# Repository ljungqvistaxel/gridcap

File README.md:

# Robust Positional Force Sensing Using Metal Over Capacitive Touch

This repository contains software, PCB design files, and 3D models used in the research with the title as above, as well as the collected data. The research investigates the use of metal over cap in a 2D matrix to meassure applied force at different parts of the sensor module. The data collected ad used in the research is also included in this repository.

## Used hardware and components

Gridcap module: 
- stm32f401re, charges/discharges pads and reads charging time with a 11.9 ns resolution, and sends the pads charging time over UART.
- 20x20 aluminium extrution (any standard length works, as long as its long enough).
- 220 kOhm resistor for pad charging.
- 74HC4067PW-Q100J MUX (4x), found at: https://www.mouser.se/ProductDetail/Nexperia/74HC4067PW-Q100J?qs=sPdA%252BpIfi%2F%252BXvXN1KGf9sg%3D%3D
- 0.5mm, 0.7mm or 1.0mm thich aluminium metal sheet (110mm x 110mm).
- SN74HC14N schmitt trigger, found at: https://www.digikey.se/sv/products/detail/texas-instruments/SN74HC14N/277223

Test rig:
- HX711 loadcell amplifier, found at: https://www.electrokit.com/forstarkare-for-lastceller-hx711
- 10kg rated loadcell, found at: https://www.electrokit.com/lastcell-10kg

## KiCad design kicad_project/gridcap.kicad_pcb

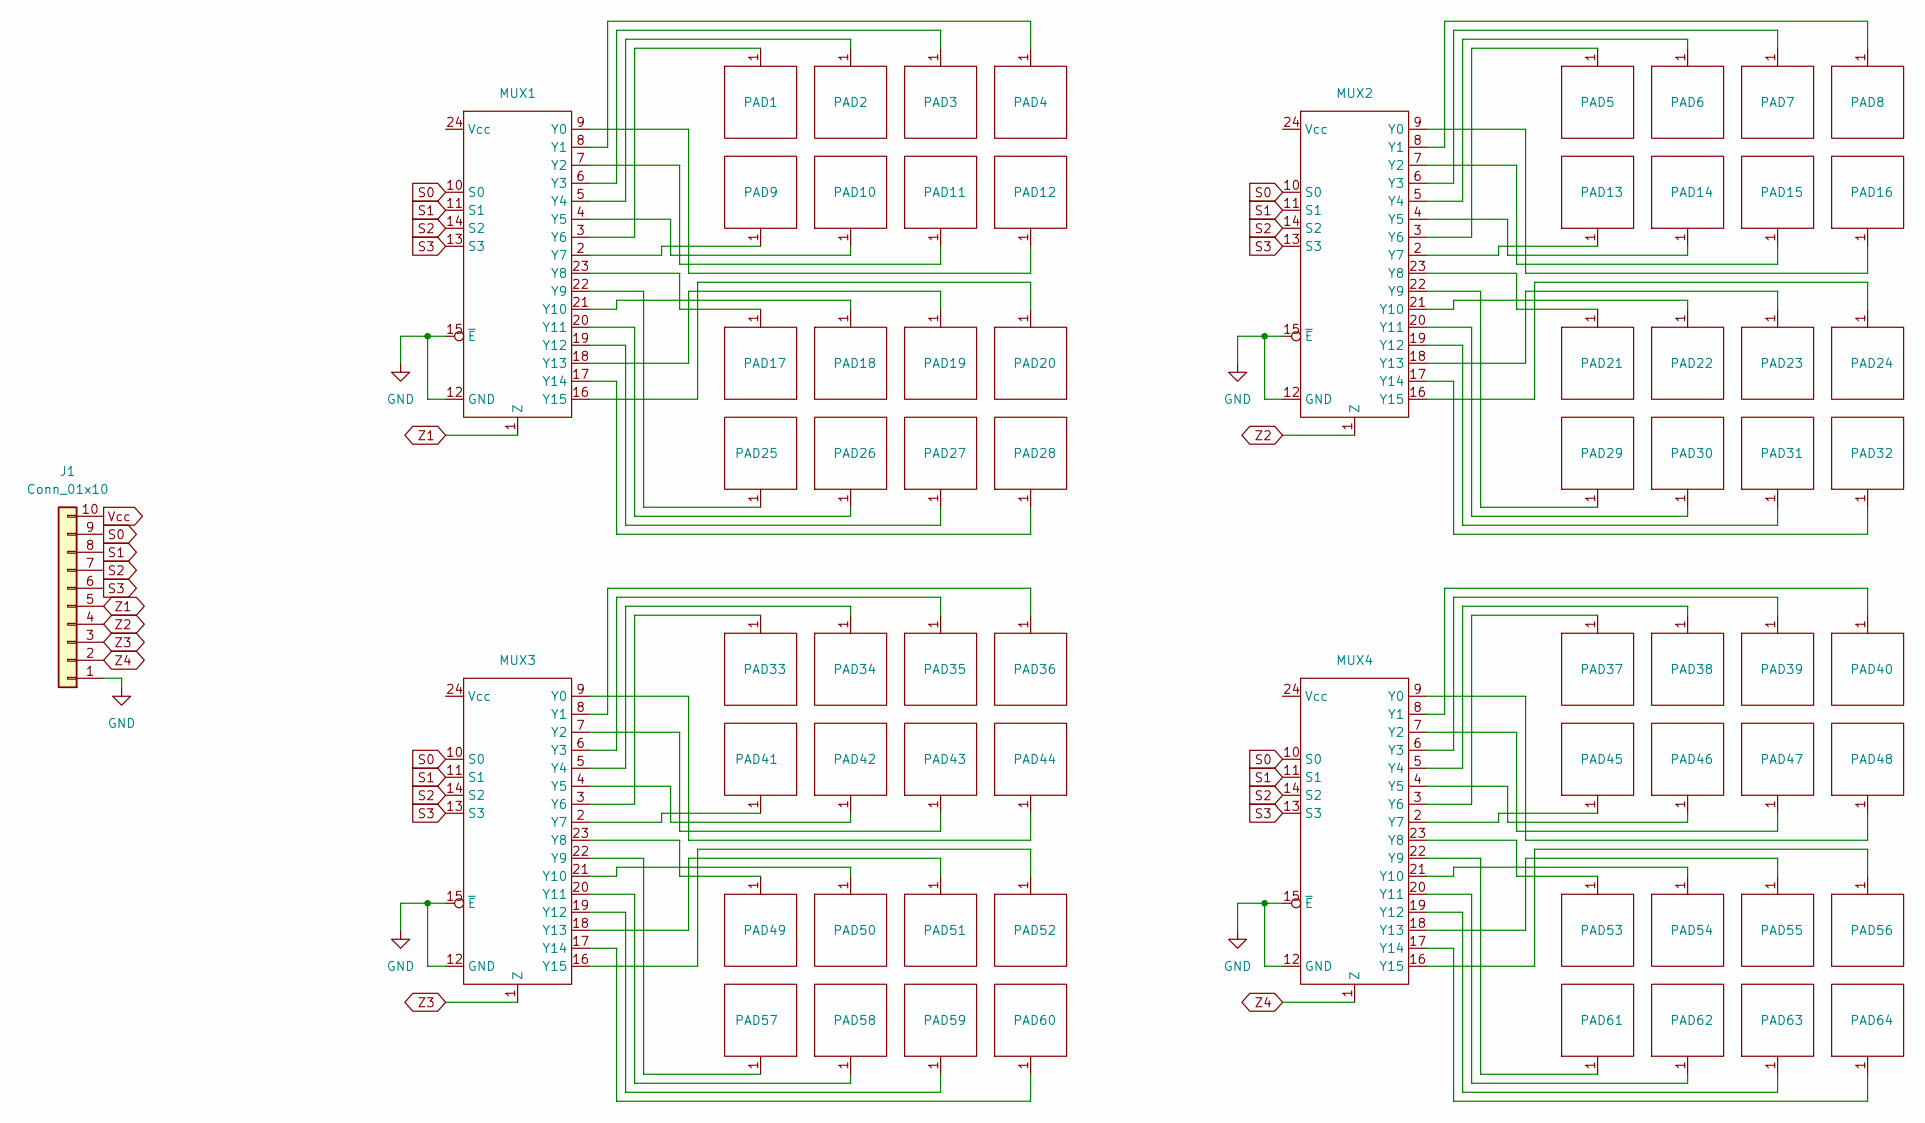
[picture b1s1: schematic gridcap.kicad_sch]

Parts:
J1: Conn_01x10
MUX1, MUX2, MUX3, MUX4: 74HC4067PW-Q100J
PAD1, PAD2, PAD3, PAD4, PAD5, PAD6, PAD7, PAD8, PAD9, PAD10, PAD11, PAD12, PAD13, PAD14, PAD15, PAD16, PAD17, PAD18, PAD19, PAD20, PAD21, PAD22, PAD23, PAD24, PAD25, PAD26, PAD27, PAD28, PAD29, PAD30, PAD31, PAD32, PAD33, PAD34, PAD35, PAD36, PAD37, PAD38, PAD39, PAD40, PAD41, PAD42, PAD43, PAD44, PAD45, PAD46, PAD47, PAD48, PAD49, PAD50, PAD51, PAD52, PAD53, PAD54, PAD55, PAD56, PAD57, PAD58, PAD59, PAD60, PAD61, PAD62, PAD63, PAD64: CAPACITOR_PAD

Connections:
GND: J1.1, MUX1.12 (GND), MUX1.15 (~E), MUX2.12 (GND), MUX2.15 (~E), MUX3.12 (GND), MUX3.15 (~E), MUX4.12 (GND), MUX4.15 (~E)
unnamed: MUX1.9 (Y0), PAD12.1
unnamed: MUX1.8 (Y1), PAD4.1
unnamed: MUX1.7 (Y2), PAD11.1
unnamed: MUX1.6 (Y3), PAD3.1
unnamed: MUX1.5 (Y4), PAD2.1
unnamed: MUX1.4 (Y5), PAD10.1
unnamed: MUX1.3 (Y6), PAD1.1
unnamed: MUX1.2 (Y7), PAD9.1
unnamed: MUX1.23 (Y8), PAD17.1
unnamed: MUX1.22 (Y9), PAD25.1
unnamed: MUX1.21 (Y10), PAD18.1
unnamed: MUX1.20 (Y11), PAD26.1
unnamed: MUX1.19 (Y12), PAD27.1
unnamed: MUX1.18 (Y13), PAD19.1
unnamed: MUX1.17 (Y14), PAD28.1
unnamed: MUX1.16 (Y15), PAD20.1
unnamed: MUX2.9 (Y0), PAD16.1
unnamed: MUX2.8 (Y1), PAD8.1
unnamed: MUX2.7 (Y2), PAD15.1
unnamed: MUX2.6 (Y3), PAD7.1
unnamed: MUX2.5 (Y4), PAD6.1
unnamed: MUX2.4 (Y5), PAD14.1
unnamed: MUX2.3 (Y6), PAD5.1
unnamed: MUX2.2 (Y7), PAD13.1
unnamed: MUX2.23 (Y8), PAD21.1
unnamed: MUX2.22 (Y9), PAD29.1
unnamed: MUX2.21 (Y10), PAD22.1
unnamed: MUX2.20 (Y11), PAD30.1
unnamed: MUX2.19 (Y12), PAD31.1
unnamed: MUX2.18 (Y13), PAD23.1
unnamed: MUX2.17 (Y14), PAD32.1
unnamed: MUX2.16 (Y15), PAD24.1
unnamed: MUX3.9 (Y0), PAD44.1
unnamed: MUX3.8 (Y1), PAD36.1
unnamed: MUX3.7 (Y2), PAD43.1
unnamed: MUX3.6 (Y3), PAD35.1
unnamed: MUX3.5 (Y4), PAD34.1
unnamed: MUX3.4 (Y5), PAD42.1
unnamed: MUX3.3 (Y6), PAD33.1
unnamed: MUX3.2 (Y7), PAD41.1
unnamed: MUX3.23 (Y8), PAD49.1
unnamed: MUX3.22 (Y9), PAD57.1
unnamed: MUX3.21 (Y10), PAD50.1
unnamed: MUX3.20 (Y11), PAD58.1
unnamed: MUX3.19 (Y12), PAD59.1
unnamed: MUX3.18 (Y13), PAD51.1
unnamed: MUX3.17 (Y14), PAD60.1
unnamed: MUX3.16 (Y15), PAD52.1
unnamed: MUX4.9 (Y0), PAD48.1
unnamed: MUX4.8 (Y1), PAD40.1
unnamed: MUX4.7 (Y2), PAD47.1
unnamed: MUX4.6 (Y3), PAD39.1
unnamed: MUX4.5 (Y4), PAD38.1
unnamed: MUX4.4 (Y5), PAD46.1
unnamed: MUX4.3 (Y6), PAD37.1
unnamed: MUX4.2 (Y7), PAD45.1
unnamed: MUX4.23 (Y8), PAD53.1
unnamed: MUX4.22 (Y9), PAD61.1
unnamed: MUX4.21 (Y10), PAD54.1
unnamed: MUX4.20 (Y11), PAD62.1
unnamed: MUX4.19 (Y12), PAD63.1
unnamed: MUX4.18 (Y13), PAD55.1
unnamed: MUX4.17 (Y14), PAD64.1
unnamed: MUX4.16 (Y15), PAD56.1
S0: J1.9, MUX1.10 (S0), MUX2.10 (S0), MUX3.10 (S0), MUX4.10 (S0)
S1: J1.8, MUX1.11 (S1), MUX2.11 (S1), MUX3.11 (S1), MUX4.11 (S1)
S2: J1.7, MUX1.14 (S2), MUX2.14 (S2), MUX3.14 (S2), MUX4.14 (S2)
S3: J1.6, MUX1.13 (S3), MUX2.13 (S3), MUX3.13 (S3), MUX4.13 (S3)
Vcc: J1.10, MUX1.24 (Vcc), MUX2.24 (Vcc), MUX3.24 (Vcc), MUX4.24 (Vcc)
Z1: J1.5, MUX1.1 (Z)
Z2: J1.4, MUX2.1 (Z)
Z3: J1.3, MUX3.1 (Z)
Z4: J1.2, MUX4.1 (Z)

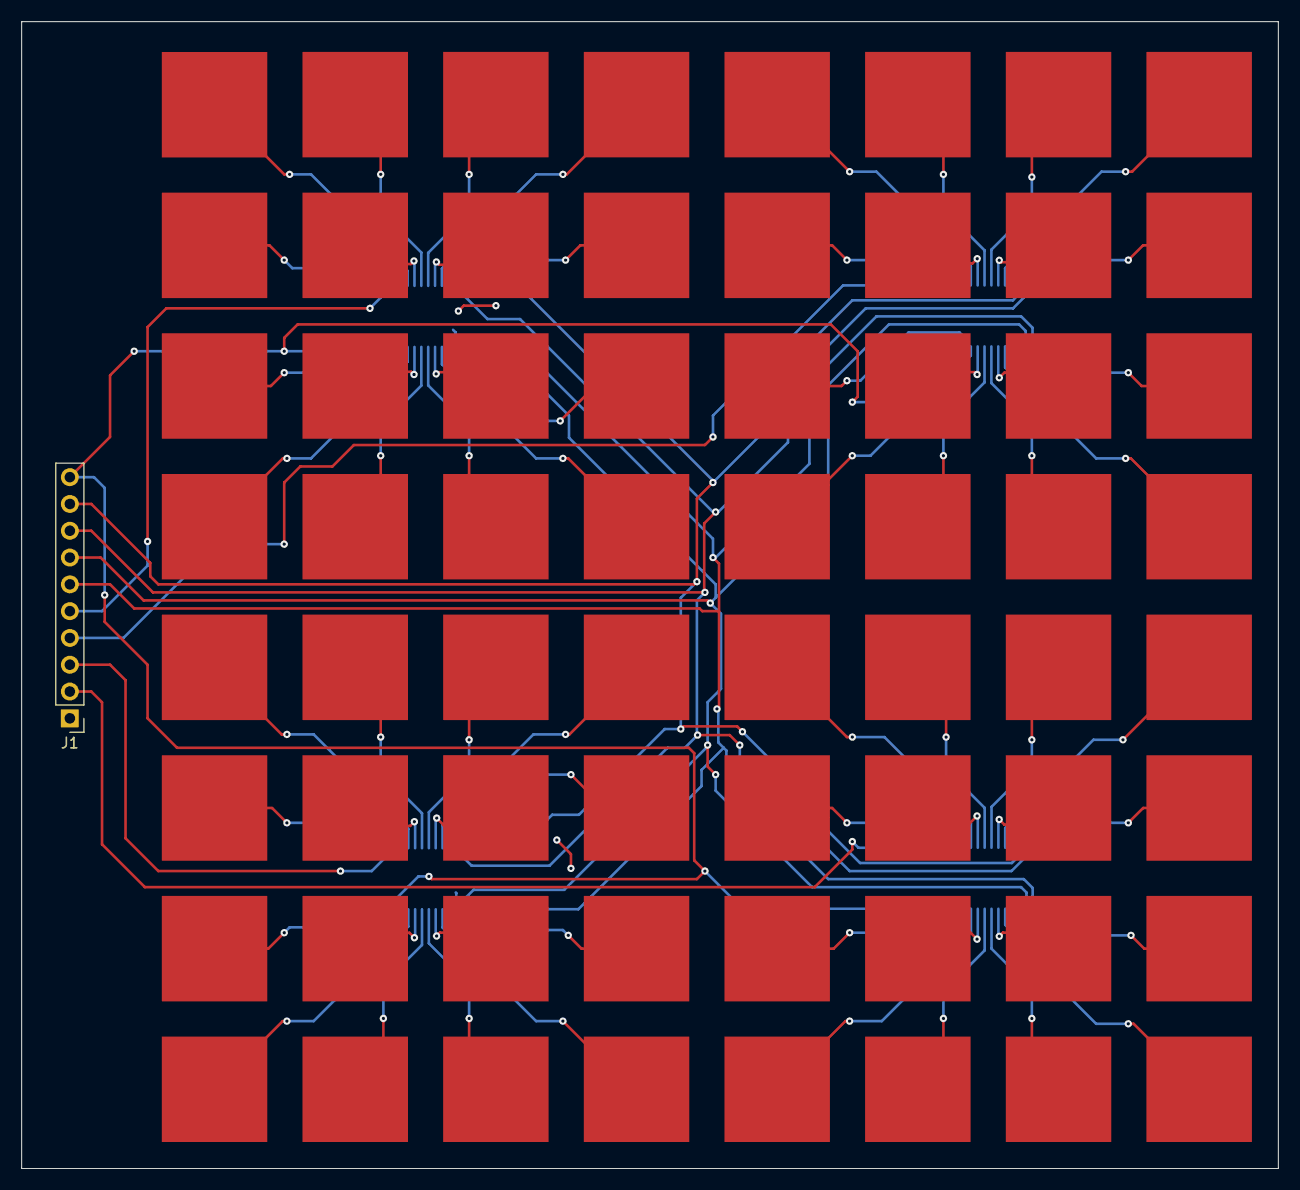
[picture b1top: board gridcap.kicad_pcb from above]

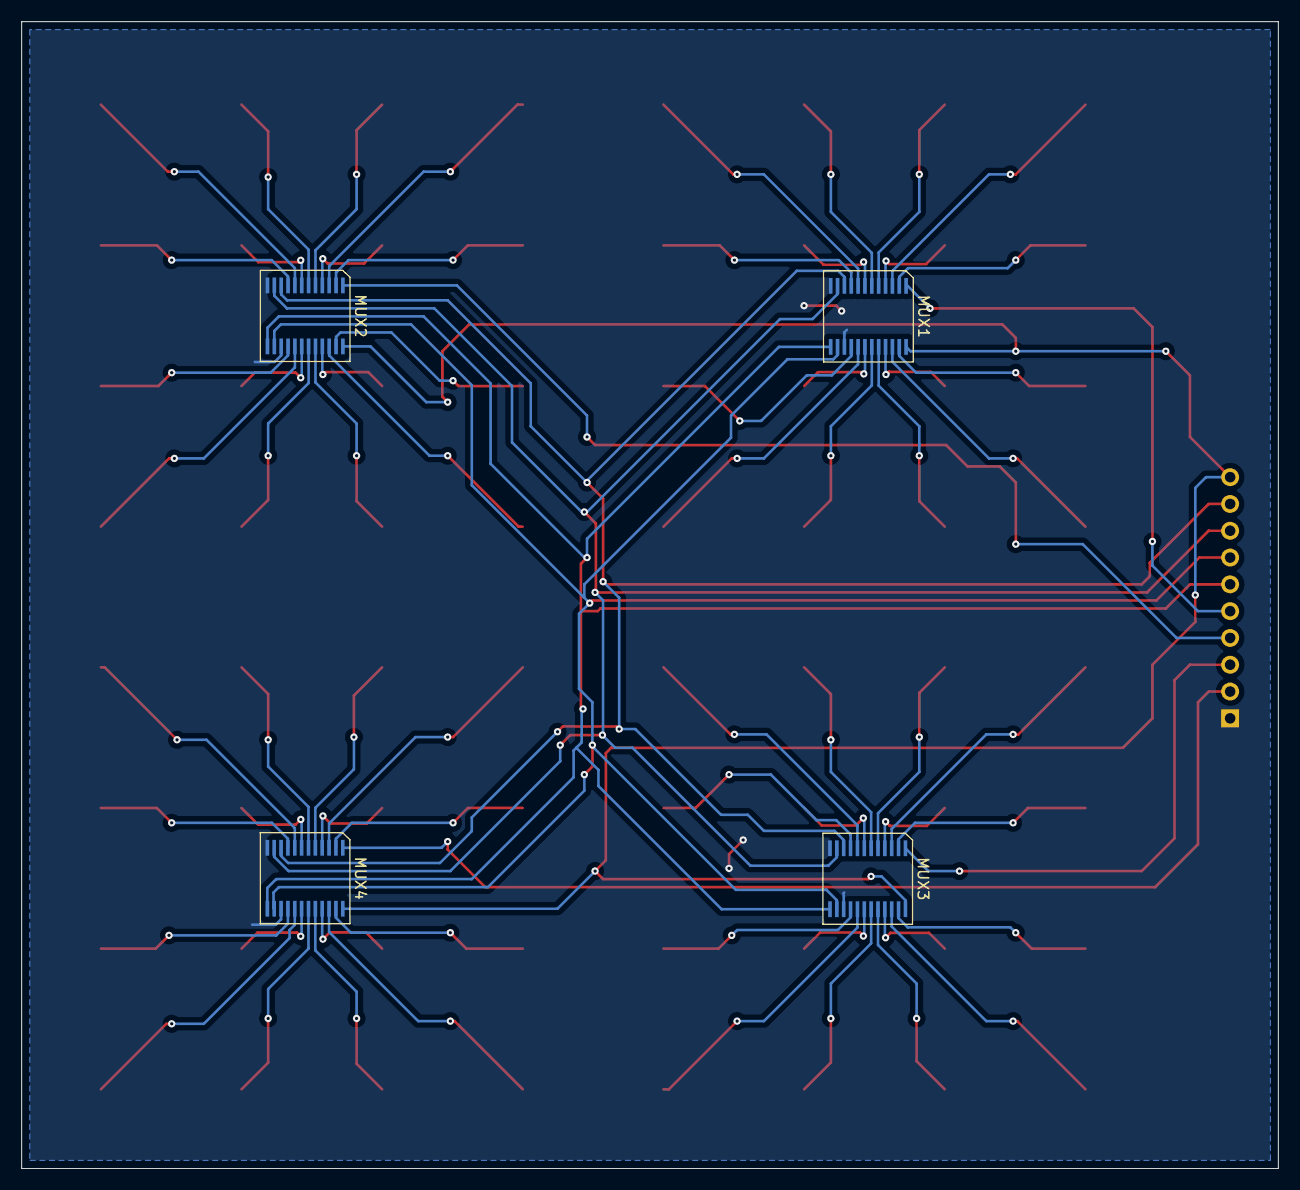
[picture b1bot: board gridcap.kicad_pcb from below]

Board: 2 copper layers, 119.1 x 108.7 mm, 69 parts (4 on the bottom side), 74 nets.

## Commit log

2024-02-02 Add .gitignore
2024-02-02 Add KiCad project and gitignore
2024-02-06 Add schematic sketches
2024-02-06 Add symbols and footprints for cap-pads and mux
2024-02-06 Add muxes and pads to schematic and begin pcb layout
2024-02-06 Add all pads to pcb
2024-02-06 Update footprint of pad
2024-02-06 Fix pad pin number
2024-02-12 Begin rewiring pads and muxes
2024-02-12 Route one mux on pcb
2024-02-12 Route all muxes to pads
2024-02-12 Route all muxes and add pcb shape
2024-02-12 Fix ground plane connections
2024-02-13 Space out tracks on pcb
    Meant to reduce signal noice between tracks
2024-02-13 Make MUX-pads longer
2024-02-13 Fix mux footprint silkscreen
2024-02-14 .gitignore plot folders and change plot settings
2024-02-24 beginning of test rig design
2024-02-24 add reader schematic
2024-02-24 Rotate foot 45deg
2024-02-25 unknown change
2024-02-26 Fix pcb design to fit cogra limitations
2024-02-26 Change to fit aisler limitations and add plugin for aisler
2024-02-27 Add x-axis, z-cap and press handle
2024-02-27 Rename x-axis and remove unused 2020 extrusion
2024-02-27 Add gitignore for FreeCAD
2024-02-27 Add software folder with gitignore for STM32
2024-02-27 Move stm32 gitignore to repo gitignore
2024-02-28 Add project for precalculating capacitance matrix
    calculations/ main.c and basic CMakeFiles.txt
2024-02-29 revert .gitignore to stm project folder
2024-02-29 move calculations into software
2024-02-29 Add stm32 project
2024-02-29 Start setup adc-dma
2024-02-29 add dma and adc
2024-03-01 Add project for uart host
2024-03-01 Add dirs for src and include files and update CMakeLists accordingly
2024-03-01 Setup timer interrupt in cubeMx with 10kHz/100us
2024-03-01 Setup code for IT
2024-03-04 Implement preliminary tim_IT
2024-03-04 implement average_reading()
2024-03-04 Update mounting holes for load cell
2024-03-04 Add load cell model to test rig
2024-03-04 Add cable routing
2024-03-04 Add GPIO ports
2024-03-05 Filter precalc graph
2024-03-05 Add src and include dirs for calculations program
2024-03-05 export header file from cap calculation program
2024-03-05 Initiate usage of single adc_channel
2024-03-07 Implement function to switch mux output
2024-03-07 Move ADC ch switching to its own function
2024-03-07 Fix ADC channel switching
    You apparently need to stop the dma when changing adc registers...
2024-03-07 Adjust get_adc_scaling
2024-03-09 Adjust update method for adc_scale
2024-03-09 Add cap-calculations header file
2024-03-09 Bitshift adc values to 8-bit
    To scale it to values 0-255
2024-03-09 Add pad-nbr variable
    For sending UART :)
2024-03-10 Add UART transmition
2024-03-10 Fix bug in IT and cleanup code
2024-03-11 Cleanup code
2024-03-11 Read UART messages from STM32
2024-03-11 Speedup ADC with 8 bit and timer
2024-03-12 Calculate caps on set frequency
2024-03-12 Convert time to capacitance
2024-03-12 Change capacitance reading method
2024-03-12 Add menu in uart_host
2024-03-12 Read charge time :)
2024-03-12 Stable capacitance reading with one schmitt trigger
2024-03-12 Calculate capacitance from nanoseconds instead
2024-03-15 Add startup arduino project
2024-03-15 Add loadcell reading ex-code
2024-03-19 Calibrate loadcell somewhat
2024-03-19 Adjust mux switching
2024-03-19 Total charging pins from 1 to 4
2024-03-19 Make use of 4 schmitt triggers
2024-03-19 Change S0 to S3 pins
2024-03-19 Add mux map for uart host
2024-03-20 Stable pad charge time readings
2024-03-20 Replace ms delays with us delays
    For faster processing!
2024-03-20 Adjust uart host constants
2024-03-21 Final calibration
2024-03-21 Change file & project name
2024-03-21 Remove unused cap_matrix file
2024-03-22 Change order of pin reading stm32
2024-03-22 handle uart comm in bg thread
2024-03-23 Add color to cap visualization
2024-03-25 fix connection error
    connected again eventough it already was
2024-03-25 adjust visualization to be square
2024-03-25 add vscode workspace to gitignore
2024-03-28 add: saving test data
2024-03-28 Speed up print output
2024-03-28 Implement for separateing tared data and not tared data
2024-03-28 Offset tared data
2024-03-28 Change unclear variable name tared to is_offset
2024-04-02 remove old unused calculation program
2024-04-02 plot max cap graph with matplotlib
2024-04-02 rename data to support multiple sample points
2024-04-02 adjust opn_readings for use in main.py
2024-04-02 add main.py to loop through test data
2024-04-02 plot all positions in the same window
2024-04-03 add more readings and calculate radius affected
2024-04-08 adjust title for graphs
2024-04-08 Add empty load command for uart host
2024-04-08 add ability to load and show data
2024-04-09 Added Schmitt to schematic
2024-04-09 Adjust resistance in schematic
2024-05-12 Raise multisampling of time to 50 times
2024-05-12 Add test data and plot capacitance response
2024-05-12 plot radius per force
2024-05-12 finish plot mean radius per force
2024-05-12 save plots as png
2024-05-12 update settings for capacitance calculations
2024-05-12 fix: remove virtual tare
2024-05-12 change title of plot
2024-05-12 Add calcuations for positional accuracy
2024-05-12 Make pos acc graph nicer with info
2024-05-12 Add lables to lines and also make them thicc ;)
2024-05-12 Fix typo
2024-05-12 change axis description of positional accuracy
2024-05-12 Change text of pos acc y axis
2024-05-14 add 0 to radius graph
2024-05-15 plot all sheet spreads
2024-05-21 Update reading schematic to 220kohm
2024-06-09 update root readme
2024-06-10 Move step files and add gridcap base step
2024-06-12 Rm old readings & add readme for software
2024-06-12 add x-axis step file
2024-06-12 remove old sketches
